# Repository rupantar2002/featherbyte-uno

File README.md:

<div align="center">

  # Featherbyte Uno

  **A RISC-V development board in the Arduino Uno footprint.**

  USB-C • Arduino-compatible headers • CAN • Open hardware

  [Hardware](#hardware) · [References](#reference-documents) · [Getting started](#getting-started) · [Manufacturing](#manufacturing) · [Project status](#project-status)
</div>

Featherbyte Uno brings the WCH **CH32V203** RISC-V microcontroller to the familiar Arduino Uno form factor. It is designed for projects that want the practical shield ecosystem, generous headers, modern USB-C connectivity, and a hardware CAN interface in one open, inspectable board design.

> [!WARNING]
> This is an active hardware project, not yet a production-qualified board. Review the design files and validate the board for your use case before ordering or deploying hardware.

## Capabilities

| | Featherbyte Uno provides |
| --- | --- |
| **Compute** | WCH CH32V203CxT6, a 32-bit RISC-V MCU based on WCH's QingKe V4B core |
| **Form factor** | Arduino Uno–compatible header layout, board outline, and mounting pattern |
| **USB** | Two USB-C receptacles: a USB device/power-input connection and a USB host + device/power-input connection |
| **Field bus** | On-board TJA1050 high-speed CAN transceiver with a screw terminal for CANH/CANL |
| **Debug** | Dedicated SWD programming/debug header |
| **Boot control** | BOOT0 push button and BOOT1 selection jumper |
| **Power & protection** | 5 V and 3.3 V header rails, USB protection, and labelled power connections |
| **Design source** | Native KiCad schematic, PCB, symbols, footprints, 3D models, and Gerbers |

## Hardware

The board preserves the recognizable Uno layout while exposing CH32V203 GPIO on the standard-style digital and analog header positions. The front side carries both USB-C connections, the MCU, boot/reset controls, CAN terminal, and the Arduino-compatible headers. The reverse side provides a clearly labelled SWD header and additional breakout access.

### Key interfaces

| Interface | What it is for |
| --- | --- |
| **USB1 / USB-C device** | Device-mode connection and power input |
| **USB2 / USB-C host + device** | USB host/device connection and power input |
| **CAN** | High-speed CAN through the TJA1050 transceiver and CANH/CANL terminal |
| **SWD** | SWDIO, SWCLK, NRST, 3.3 V, and GND for programming and debugging |
| **Arduino headers** | Digital, analog, power, I²C, and SPI-style expansion in the Uno form factor |

## Hardware validation

The images above show an assembled Featherbyte Uno prototype on the bench.

> [!CAUTION]
> These photographs show an **early board revision**. The current KiCad project includes silkscreen corrections and additions that are not reflected on this prototype. Treat the checked-in design files as the source of truth for the current revision.

### Blink test on real hardware

*A blink test running on the assembled prototype. This demonstrates basic firmware execution on real hardware; it does not constitute full board validation.*

## Repository map

```text
.
├── hardware/
│   └── featherbyte-uno-v1.0.0/
│       ├── featherbyte-uno-v1.0.0.kicad_pro  # KiCad project
│       ├── featherbyte-uno-v1.0.0.kicad_sch  # schematic
│       ├── featherbyte-uno-v1.0.0.kicad_pcb  # PCB layout
│       ├── Gerber/                           # fabrication outputs
│       ├── 3d/                               # component STEP models
│       ├── footprints/                       # custom footprints
│       └── sym/                              # project symbol libraries
├── docs/                                     # schematic and component references
└── images/                                   # board renders used here
```

## Reference documents

The documents below are checked into the repository for offline design review and bring-up.

| Document | Purpose |
| --- | --- |
| [Featherbyte Uno schematics v1.2.0](docs/schematics-v1.2.0.pdf) | Current schematic reference export |
| [CH32V203 datasheet](docs/CH32V203DS0.PDF) | MCU electrical characteristics, pin functions, and package details |
| [CH32FV2x / V3x reference manual](docs/CH32FV2x_V3xRM.PDF) | MCU peripherals, registers, and programming reference |
| [QingKe V4 processor manual](docs/QingKeV4_Processor_Manual.PDF) | RISC-V core architecture and instruction-set reference |
| [TJA1050 datasheet](docs/TJA1050.pdf) | High-speed CAN transceiver reference |

## Getting started

### Explore or modify the board

1. Install [KiCad](https://www.kicad.org/download/).
2. Clone this repository.
3. Open [`hardware/featherbyte-uno-v1.0.0/featherbyte-uno-v1.0.0.kicad_pro`](hardware/featherbyte-uno-v1.0.0/featherbyte-uno-v1.0.0.kicad_pro) in KiCad.
4. Use the schematic and PCB editors to inspect the design; the project-local symbol, footprint, and 3D-model assets are included.

### Program and debug

The board exposes an SWD header labelled **SWDIO**, **SWCLK**, **NRST**, **3.3V**, and **GND**. Connect a compatible 3.3 V SWD debugger to this header. Firmware, toolchain, bootloader, and flashing instructions are not yet included in this repository—please treat bring-up as development work until those are published.

## Manufacturing

Ready-to-export fabrication files are in [`hardware/featherbyte-uno-v1.0.0/Gerber`](hardware/featherbyte-uno-v1.0.0/Gerber). Before submitting an order:

1. Check the Gerbers and drill files in your fabricator’s viewer.
2. Confirm stack-up, finish, thickness, and assembly constraints against your requirements.
3. Independently verify the schematic, PCB revision, and component availability.
4. Bring up and test a small batch before any larger build.

The included hardware project identifies the current schematic revision as **v1.2.0**. The directory name is retained as `featherbyte-uno-v1.0.0` to match the checked-in project and fabrication paths.

## Project status

| Area | Status |
| --- | --- |
| KiCad source | Available |
| Gerber fabrication outputs | Available |
| PCB renders | Available |
| Firmware and examples | Not yet published here |
| BOM / assembly documentation | Not yet published here |
| License | [MIT License](LICENSE) |

## Contributing

Design review, testing notes, issues, and pull requests are welcome. For hardware changes, please include the relevant KiCad source changes and describe any electrical, mechanical, or manufacturing impact.

## License

[MIT License](LICENSE)

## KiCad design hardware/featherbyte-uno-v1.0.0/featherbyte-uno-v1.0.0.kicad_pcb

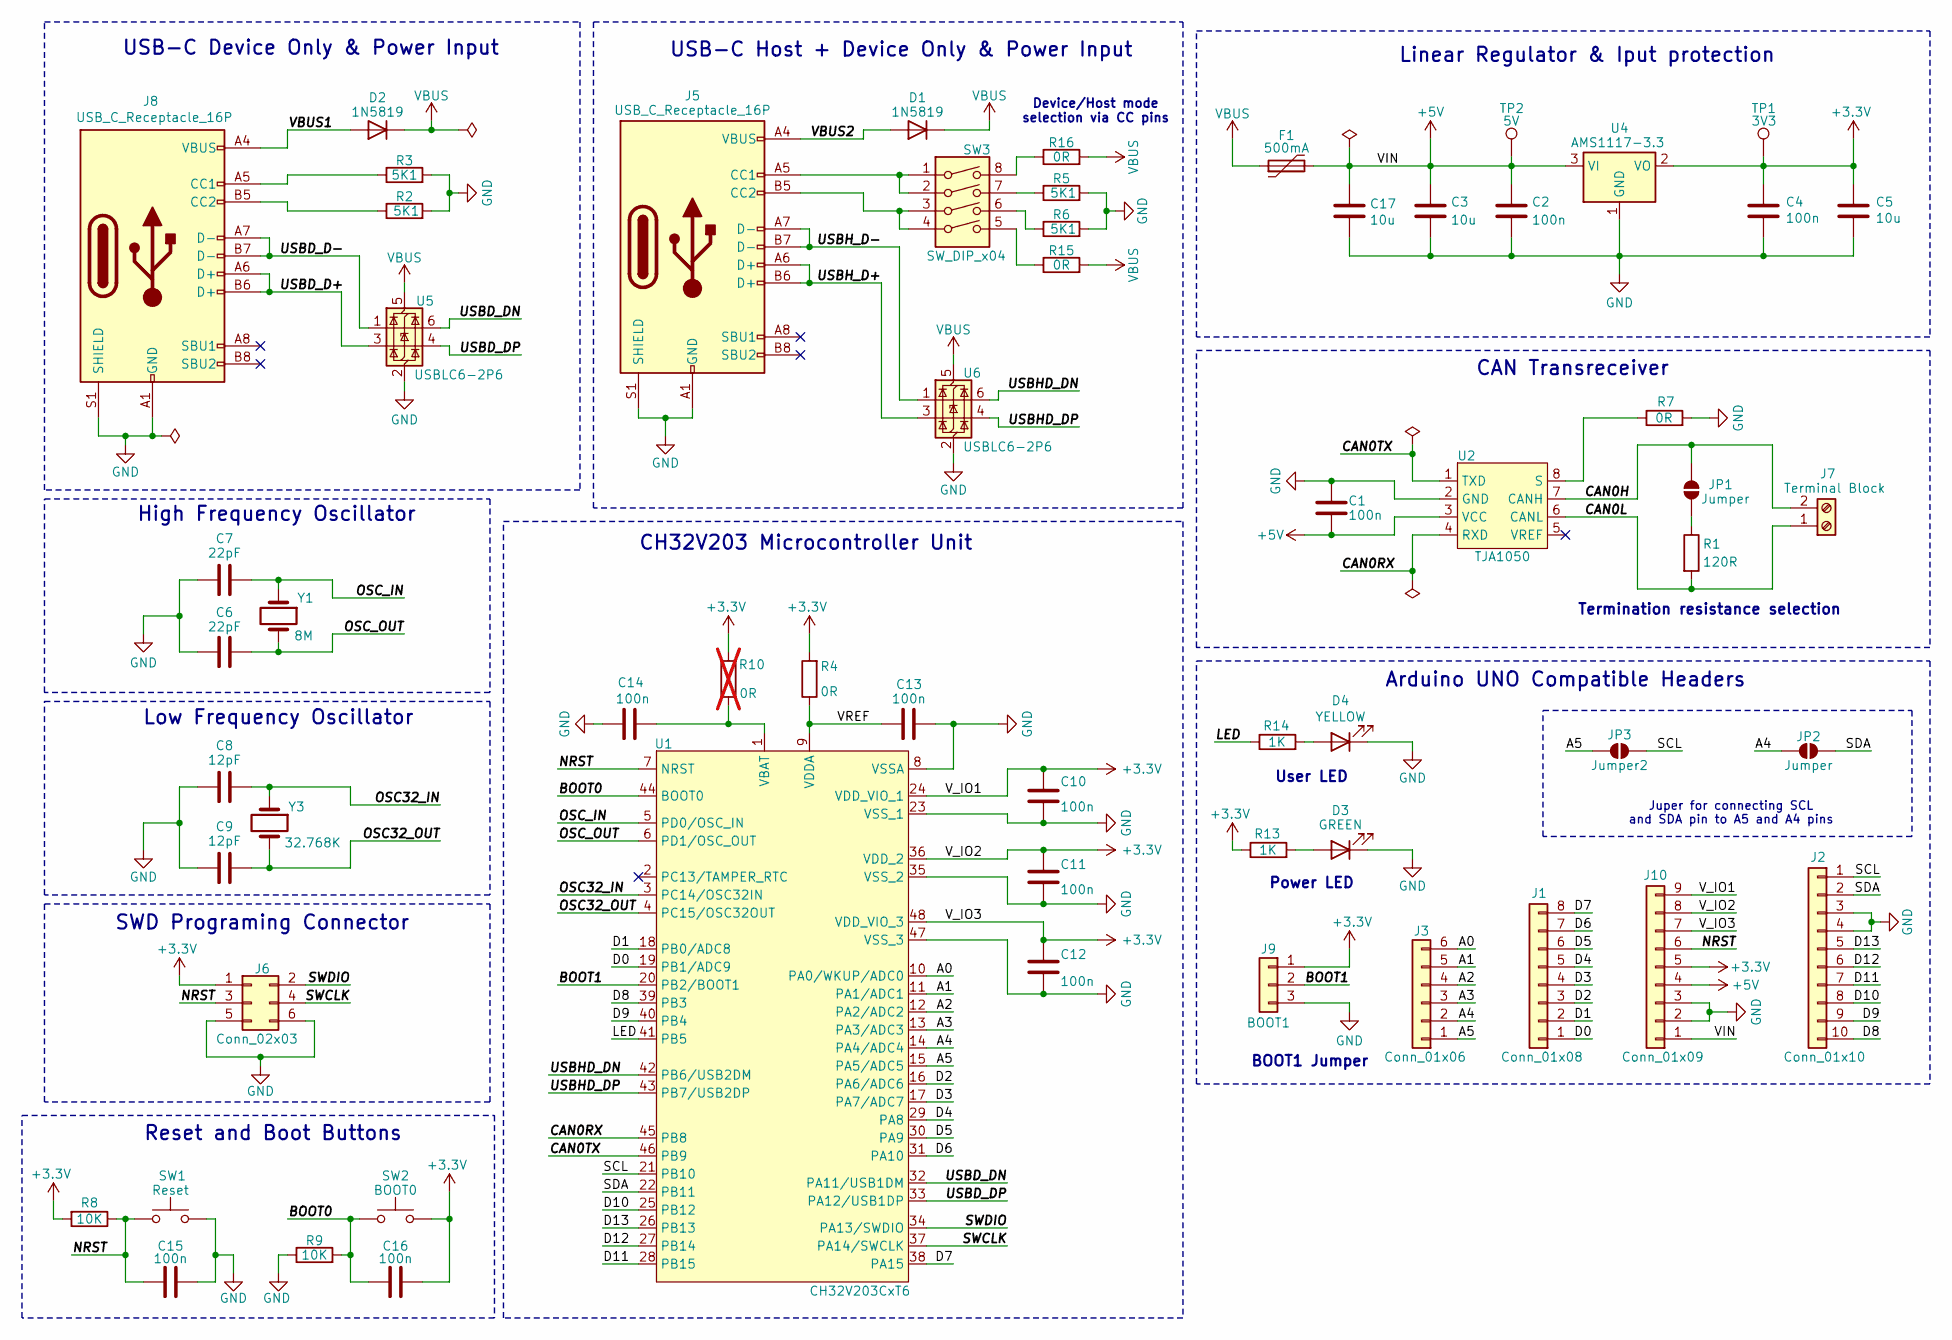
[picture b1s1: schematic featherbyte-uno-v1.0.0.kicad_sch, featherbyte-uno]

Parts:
C1, C2, C4, C10, C11, C12, C13, C14, C15, C16: 100n; C_0603_1608Metric
C3, C5, C17: 10u; C_1206_3216Metric
C6, C7: 22pF; C_0603_1608Metric
C8, C9: 12pF; C_0603_1608Metric
D1, D2: 1N5819; D_SOD-123
D3: GREEN; LED_0805_2012Metric
D4: YELLOW; LED_0805_2012Metric
F1: 500mA; Fuse_1206_3216Metric
J1: Conn_01x08; PinSocket_1x08_P2.54mm_Vertical
J2: Conn_01x10; PinSocket_1x10_P2.54mm_Vertical
J3: Conn_01x06; PinSocket_1x06_P2.54mm_Vertical
J5, J8: USB_C_Receptacle_16P; USB_C_Receptacle_HCTL_HC-TYPE-C-16P-01A
J6: Conn_02x03; PinHeader_2x03_P2.54mm_Vertical
J7: Terminal Block; TerminalBlock_MaiXu_MX126-5.0-02P_1x02_P5.00mm
J9: BOOT1; PinHeader_1x03_P2.54mm_Vertical
J10: Conn_01x09; PinSocket_1x09_P2.54mm_Vertical
JP1, JP2: Jumper; SolderJumper-2_P1.3mm_Open_TrianglePad1.0x1.5mm
JP3: Jumper2; SolderJumper-2_P1.3mm_Open_TrianglePad1.0x1.5mm
R1: 120R; R_0603_1608Metric
R2, R3, R5, R6: 5K1; R_0603_1608Metric
R4, R7, R15, R16: 0R; R_0603_1608Metric
R8, R9: 10K; R_0603_1608Metric
R10: 0R; R_0603_1608Metric; not fitted
R13, R14: 1K; R_0603_1608Metric
SW1: Reset; SW_SPST_CK_RS282G05A3
SW2: BOOT0; SW_SPST_CK_RS282G05A3
SW3: SW_DIP_x04; SW_DIP_SPSTx04_Slide_KingTek_DSHP04TS_W7.62mm_P1.27mm
TP1: 3V3; TestPoint_Pad_D1.5mm
TP2: 5V; TestPoint_Pad_D1.5mm
U1: CH32V203CxT6; LQFP-48_7x7mm_P0.5mm
U2: TJA1050; SO-8_3.9x4.9mm_P1.27mm
U4: AMS1117-3.3; SOT-223-3_TabPin2
U5, U6: USBLC6-2P6; SOT-666
Y1: 8M; Crystal_SMD_HC49-SD
Y3: 32.768K; Crystal_SMD_3215-2Pin_3.2x1.5mm

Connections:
+3.3V: C4.1, C5.1, C10.1, C11.1, C12.1, C16.2, J6.1, J9.1, J10.5, J10.7, J10.8, J10.9, R4.2, R8.2, R10.2, R13.1, SW2.2, TP1.1, U1.24 (VDD_VIO_1), U1.36 (VDD_2), U1.48 (VDD_VIO_3), U4.2 (VO)
+5V: C1.2, C2.1, C3.1, C17.1, F1.2, J10.1, J10.4, TP2.1, U2.3 (VCC), U4.3 (VI)
/A0: J3.6, U1.10 (PA0/WKUP/ADC0)
/A1: J3.5, U1.11 (PA1/ADC1)
/A2: J3.4, U1.12 (PA2/ADC2)
/A3: J3.3, U1.13 (PA3/ADC3)
/A4: J3.2, JP2.1 (A), U1.14 (PA4/ADC4)
/A5: J3.1, JP3.1 (A), U1.15 (PA5/ADC5)
/BOOT0: C16.1, R9.2, SW2.1, U1.44 (BOOT0)
/BOOT1: J9.2, U1.20 (PB2/BOOT1)
/CAN0H: J7.2, JP1.2 (B), U2.7 (CANH)
/CAN0L: J7.1, R1.2, U2.6 (CANL)
/CAN0RX: U1.45 (PB8), U2.4 (RXD)
/CAN0TX: U1.46 (PB9), U2.1 (TXD)
/D0: J1.1, U1.19 (PB1/ADC9)
/D1: J1.2, U1.18 (PB0/ADC8)
/D2: J1.3, U1.16 (PA6/ADC6)
/D3: J1.4, U1.17 (PA7/ADC7)
/D4: J1.5, U1.29 (PA8)
/D5: J1.6, U1.30 (PA9)
/D6: J1.7, U1.31 (PA10)
/D7: J1.8, U1.38 (PA15)
/D8: J2.10, U1.39 (PB3)
/D9: J2.9, U1.40 (PB4)
/D10: J2.8, U1.25 (PB12)
/D11: J2.7, U1.28 (PB15)
/D12: J2.6, U1.27 (PB14)
/D13: J2.5, U1.26 (PB13)
/LED: R14.1, U1.41 (PB5)
/NRST: C15.1, J6.3, J10.6, R8.1, SW1.1, U1.7 (NRST)
/OSC32_IN: C8.1, U1.3 (PC14/OSC32IN), Y3.1
/OSC32_OUT: C9.1, U1.4 (PC15/OSC32OUT), Y3.2
/OSC_IN: C7.1, U1.5 (PD0/OSC_IN), Y1.1
/OSC_OUT: C6.1, U1.6 (PD1/OSC_OUT), Y1.2
/SCL: J2.1, JP3.2 (B), U1.21 (PB10)
/SDA: J2.2, JP2.2 (B), U1.22 (PB11)
/SWCLK: J6.4, U1.37 (PA14/SWCLK)
/SWDIO: J6.2, U1.34 (PA13/SWDIO)
/USBD_D+: J8.A6 (D+), J8.B6 (D+), U5.3 (I/O2)
/USBD_D-: J8.A7 (D-), J8.B7 (D-), U5.1 (I/O1)
/USBD_DN: U1.32 (PA11/USB1DM), U5.6 (I/O1)
/USBD_DP: U1.33 (PA12/USB1DP), U5.4 (I/O2)
/USBHD_DN: U1.42 (PB6/USB2DM), U6.6 (I/O1)
/USBHD_DP: U1.43 (PB7/USB2DP), U6.4 (I/O2)
/USBH_D+: J5.A6 (D+), J5.B6 (D+), U6.3 (I/O2)
/USBH_D-: J5.A7 (D-), J5.B7 (D-), U6.1 (I/O1)
/VBUS1: D2.2 (A), J8.A4 (VBUS), J8.A9 (VBUS), J8.B4 (VBUS), J8.B9 (VBUS)
/VBUS2: D1.2 (A), J5.A4 (VBUS), J5.A9 (VBUS), J5.B4 (VBUS), J5.B9 (VBUS)
/VREF: C13.1, R4.1, U1.9 (VDDA)
GND: C1.1, C2.2, C3.2, C4.2, C5.2, C6.2, C7.2, C8.2, C9.2, C10.2, C11.2, C12.2, C13.2, C14.2, C15.2, C17.2, D3.1 (K), D4.1 (K), J2.3, J2.4, J5.A1 (GND), J5.A12 (GND), J5.B1 (GND), J5.B12 (GND), J5.S1 (SHIELD), J6.5, J6.6, J8.A1 (GND), J8.A12 (GND), J8.B1 (GND), J8.B12 (GND), J8.S1 (SHIELD), J9.3, J10.2, J10.3, R2.2, R3.2, R5.2, R6.2, R7.2, R9.1, SW1.2, U1.8 (VSSA), U1.23 (VSS_1), U1.35 (VSS_2), U1.47 (VSS_3), U2.2 (GND), U4.1 (GND), U5.2 (GND), U6.2 (GND)
unnamed: D3.2 (A), R13.2
unnamed: D4.2 (A), R14.2
unnamed: J5.A5 (CC1), SW3.1, SW3.2
unnamed: J5.B5 (CC2), SW3.3, SW3.4
unnamed: J8.A5 (CC1), R3.1
unnamed: J8.B5 (CC2), R2.1
unnamed: JP1.1 (A), R1.1
unnamed: R5.1, SW3.7
unnamed: R6.1, SW3.6
unnamed: R15.1, SW3.5
unnamed: R16.1, SW3.8
unnamed: C14.1, R10.1, U1.1 (VBAT)
unnamed: R7.1, U2.8 (S)
VBUS: D1.1 (K), D2.1 (K), F1.1, R15.2, R16.2, U5.5 (VBUS), U6.5 (VBUS)

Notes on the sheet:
Juper for connecting SCL and SDA pin to A5 and A4 pins
USB-C Device Only & Power Input
Termination resistance selection
SWD Programing Connector
BOOT1 Jumper
High Frequency Oscillator
Linear Regulator & Iput protection
Reset and Boot Buttons
Low Frequency Oscillator
Arduino UNO Compatible Headers
Power LED
CAN Transreceiver
USB-C Host + Device Only & Power Input
User LED
Device/Host mode selection via CC pins
CH32V203 Microcontroller Unit

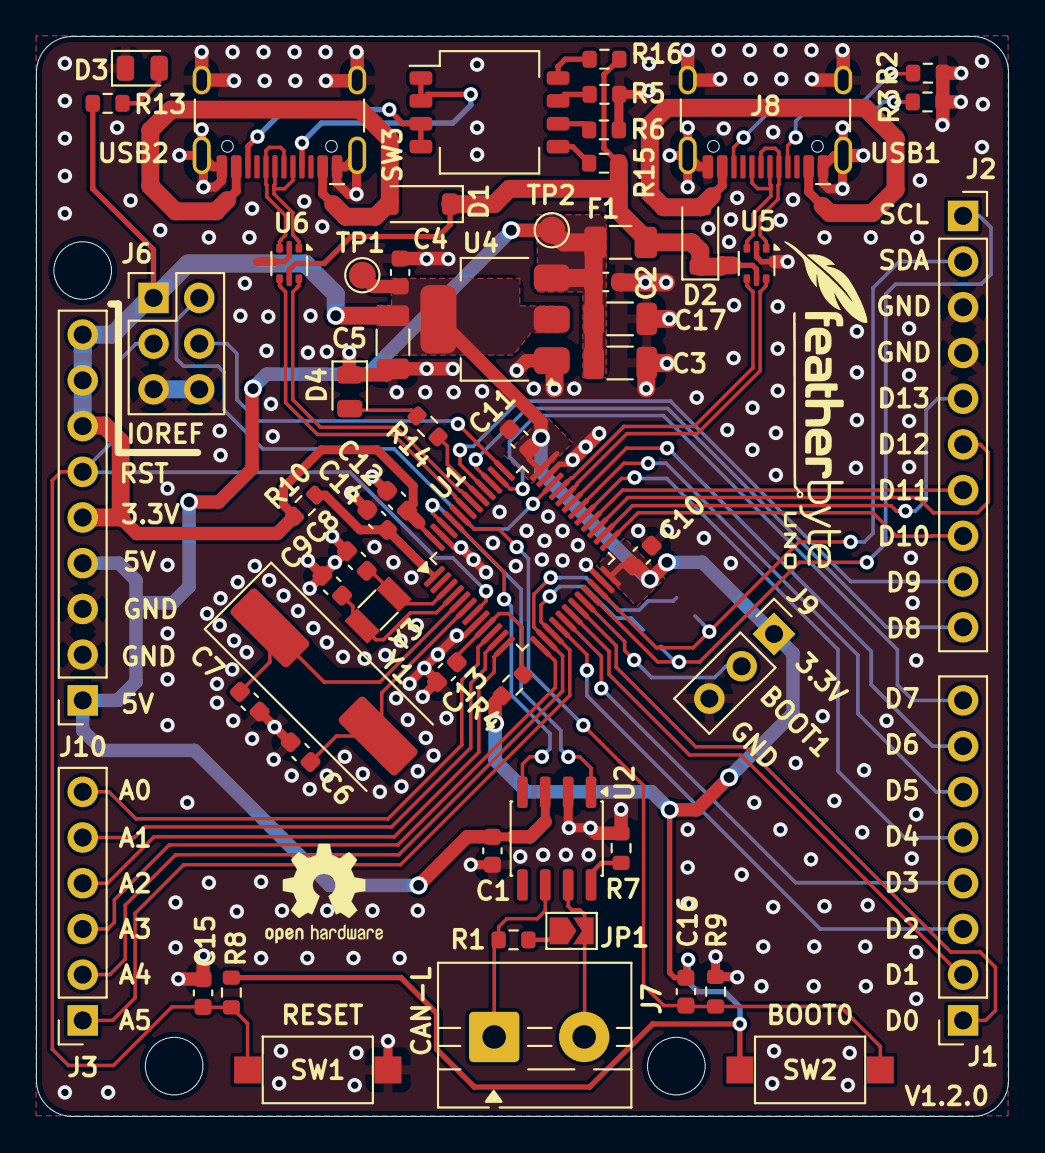
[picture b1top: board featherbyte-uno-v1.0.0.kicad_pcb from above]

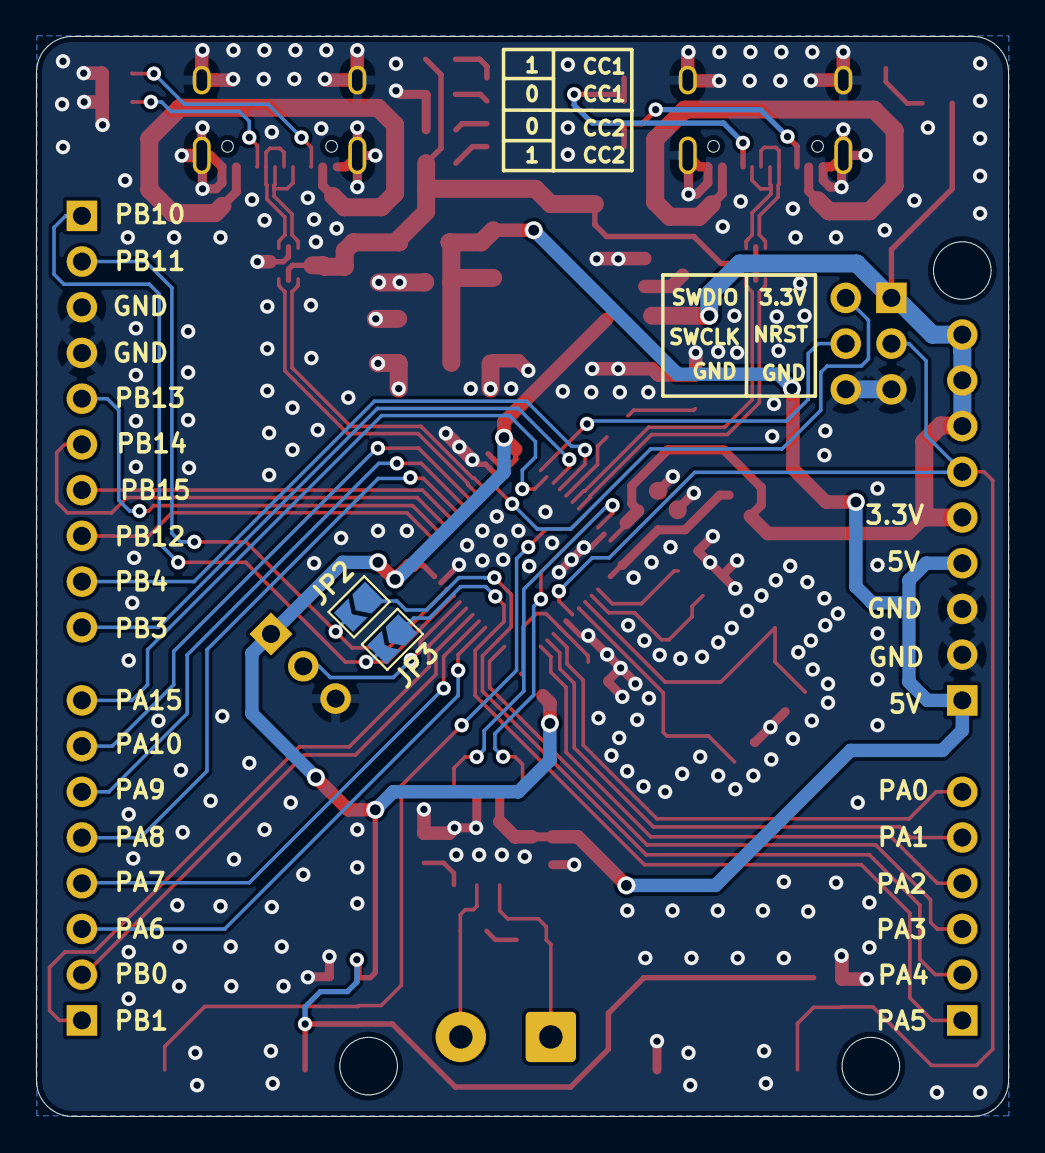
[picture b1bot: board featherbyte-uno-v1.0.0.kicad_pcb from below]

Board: 2 copper layers, 54.0 x 60.0 mm, 60 parts (2 on the bottom side), 64 nets.
